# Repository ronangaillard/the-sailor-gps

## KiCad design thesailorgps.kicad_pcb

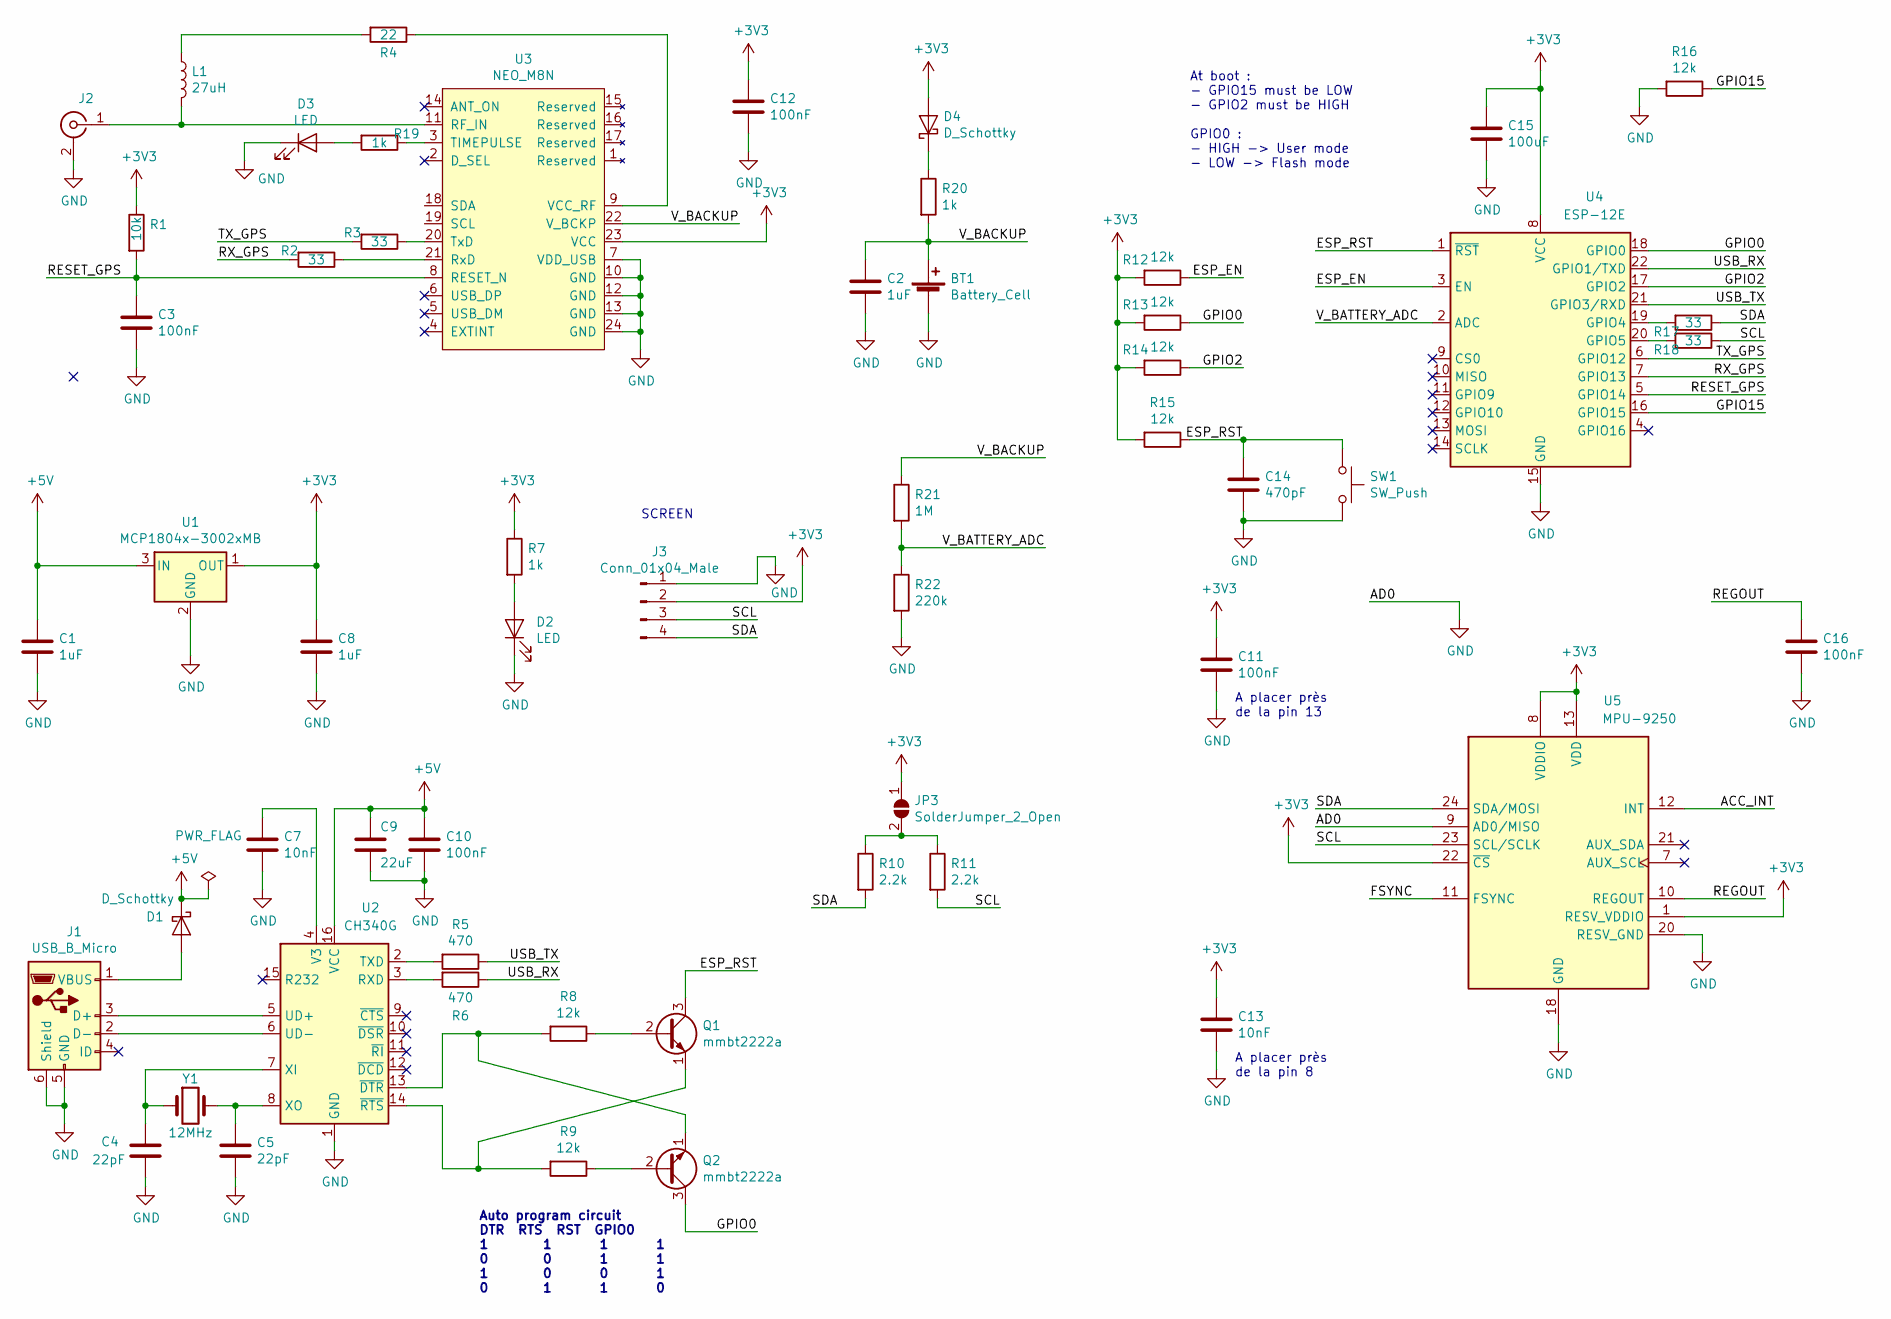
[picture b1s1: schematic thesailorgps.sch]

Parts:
BT1: Battery_Cell; 2998
C1, C2, C8: 1uF; C_0603_HandSoldering
C3, C10, C11, C12, C16: 100nF; C_0603_HandSoldering
C4, C5: 22pF; C_0603_HandSoldering
C7, C13: 10nF; C_0603_HandSoldering
C9: 22uF; C_0603_HandSoldering
C14: 470pF; C_0603_HandSoldering
C15: 100uF; C_0603_HandSoldering
D1, D4: D_Schottky; D_0603
D2, D3: LED; LED_0603_HandSoldering
J1: USB_B_Micro; MOLEX_105017-1001
J2: Conn_Coaxial; SMA_coude
J3: Conn_01x04_Male; Molex_PicoBlade_53261-0471_04x1.25mm_Angled
JP3: SolderJumper_2_Open; SolderJumper-2_P1.3mm_Open_RoundedPad1.0x1.5mm
L1: 27uH; L_0805_HandSoldering
Q1, Q2: mmbt2222a; SOT-23-3
R1: 10k; R_0603_HandSoldering
R2, R3, R17, R18: 33; R_0603_HandSoldering
R4: 22; R_0603_HandSoldering
R5, R6: 470; R_0603_HandSoldering
R7, R19, R20: 1k; R_0603_HandSoldering
R8, R9, R12, R13, R14, R15, R16: 12k; R_0603_HandSoldering
R10, R11: 2.2k; R_0603_HandSoldering
R21: 1M; R_0603_HandSoldering
R22: 220k; R_0603_HandSoldering
SW1: SW_Push; ebay_smd_button
U1: MCP1804x-3002xMB; SOT-89-3_Handsoldering
U2: CH340G; SOIC-16_3.9x9.9mm_Pitch1.27mm
U3: NEO_M8N; neo_m8n
U4: ESP-12E
U5: MPU-9250; QFN-24-1EP_3x3mm
Y1: 12MHz; Crystal_SMD_0603-2pin_6.0x3.5mm_HandSoldering

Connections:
+3V3: C8.1, C11.1, C12.1, C13.1, C15.1, D4.2 (A), J3.2, JP3.1 (A), R1.1, R7.1, R12.2, R13.2, R14.2, R15.2, U1.1 (OUT), U3.23 (VCC), U4.8 (VCC), U5.1 (RESV_VDDIO), U5.8 (VDDIO), U5.13 (VDD), U5.22 (~CS)
+5V: C1.1, C9.1, C10.1, D1.1 (K), U1.3 (IN), U2.16 (VCC)
/ACC_INT: U5.12 (INT)
/ESP_EN: R12.1, U4.3 (EN)
/ESP_RST: C14.1, Q1.3 (C), R15.1, SW1.1, U4.1 (~RST)
/FSYNC: U5.11 (FSYNC)
/GPIO0: Q2.3 (C), R13.1, U4.18 (GPIO0)
/GPIO2: R14.1, U4.17 (GPIO2)
/GPIO15: R16.1, U4.16 (GPIO15)
/REGOUT: C16.1, U5.10 (REGOUT)
/RESET_GPS: C3.1, R1.2, U3.8 (RESET_N), U4.5 (GPIO14)
/RX_GPS: R2.2, U4.7 (GPIO13)
/SCL: J3.3, R11.2, R18.1, U5.23 (SCL/SCLK)
/SDA: J3.4, R10.2, R17.1, U5.24 (SDA/MOSI)
/TX_GPS: R3.2, U4.6 (GPIO12)
/USB_RX: R6.1, U4.22 (GPIO1/TXD)
/USB_TX: R5.1, U4.21 (GPIO3/RXD)
/V_BACKUP: BT1.1 (+), C2.1, R20.2, R21.1, U3.22 (V_BCKP)
/V_BATTERY_ADC: R21.2, R22.1, U4.2 (ADC)
GND: BT1.2 (-), C1.2, C2.2, C3.2, C4.2, C5.2, C7.2, C8.2, C9.2, C10.2, C11.2, C12.2, C13.2, C14.2, C15.2, C16.2, D2.1 (K), D3.1 (K), J1.5 (GND), J1.6 (Shield), J2.2 (Ext), J3.1, R16.2, R22.2, SW1.2, U1.2 (GND), U2.1 (GND), U3.7 (VDD_USB), U3.10 (GND), U3.12 (GND), U3.13 (GND), U3.24 (GND), U4.15 (GND), U5.9 (AD0/MISO), U5.18 (GND), U5.20 (RESV_GND)
unnamed: C4.1, U2.7 (XI), Y1.1
unnamed: C5.1, U2.8 (XO), Y1.2
unnamed: C7.1, U2.4 (V3)
unnamed: D1.2 (A), J1.1 (VBUS)
unnamed: D2.2 (A), R7.2
unnamed: D3.2 (A), R19.2
unnamed: D4.1 (K), R20.1
unnamed: J1.2 (D-), U2.6 (UD-)
unnamed: J1.3 (D+), U2.5 (UD+)
unnamed: J2.1 (In), L1.2, U3.11 (RF_IN)
unnamed: JP3.2 (B), R10.1, R11.1
unnamed: L1.1, R4.2
unnamed: Q1.1 (E), R9.2, U2.14 (~RTS)
unnamed: Q1.2 (B), R8.1
unnamed: Q2.1 (E), R8.2, U2.13 (~DTR)
unnamed: Q2.2 (B), R9.1
unnamed: R2.1, U3.21 (RxD)
unnamed: R3.1, U3.20 (TxD)
unnamed: R4.1, U3.9 (VCC_RF)
unnamed: R5.2, U2.2 (TXD)
unnamed: R6.2, U2.3 (RXD)
unnamed: R17.2, U4.19 (GPIO4)
unnamed: R18.2, U4.20 (GPIO5)
unnamed: R19.1, U3.3 (TIMEPULSE)

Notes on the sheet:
SCREEN
Auto program circuit DTR RTS RST GPIO0 1 1 1 1 0 0 1 1 1 0 0 1 0 1 1 0
At boot : - GPIO15 must be LOW - GPIO2 must be HIGH GPIO0 : - HIGH -> User mode - LOW -> Flash mode
A placer près de la pin 13
A placer près de la pin 8

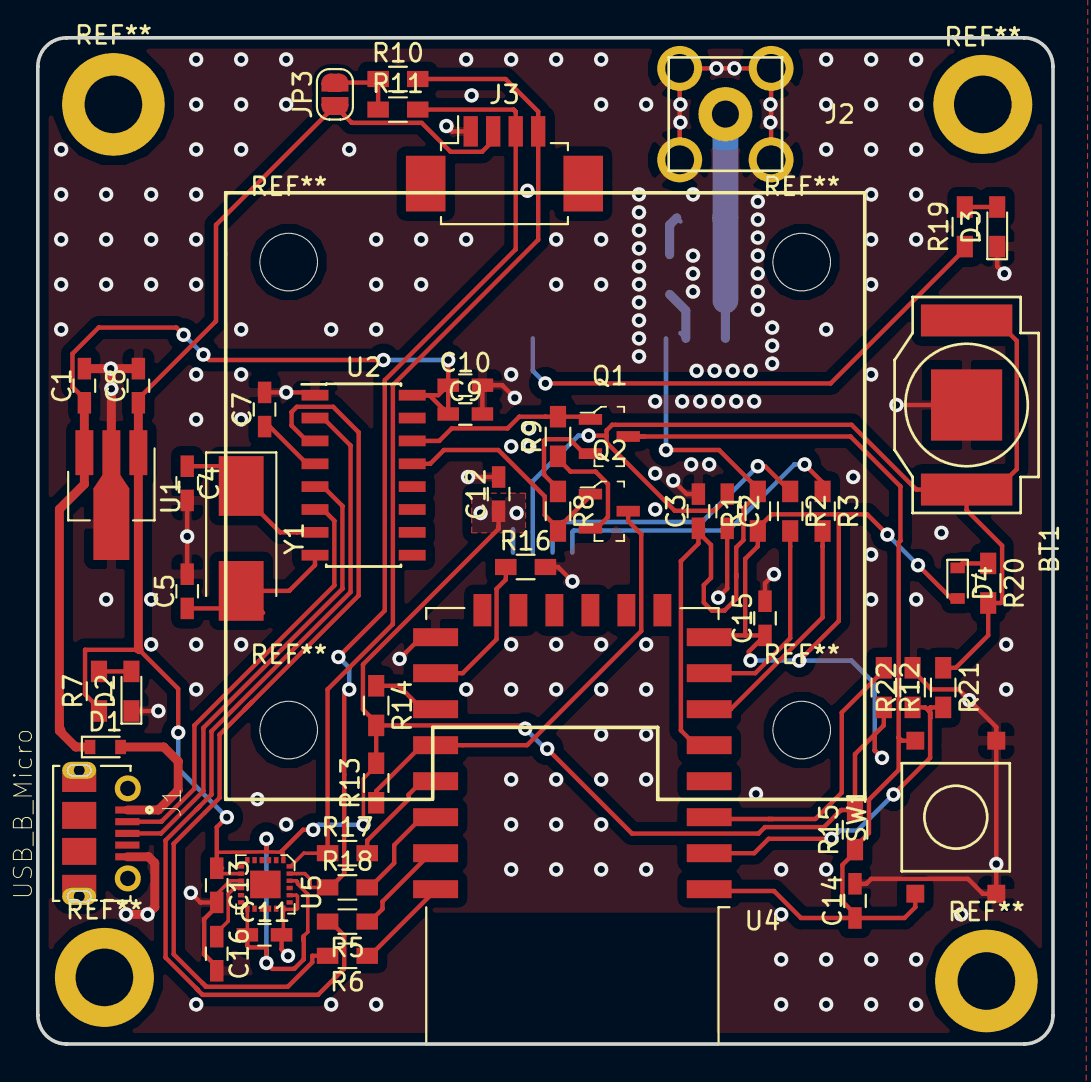
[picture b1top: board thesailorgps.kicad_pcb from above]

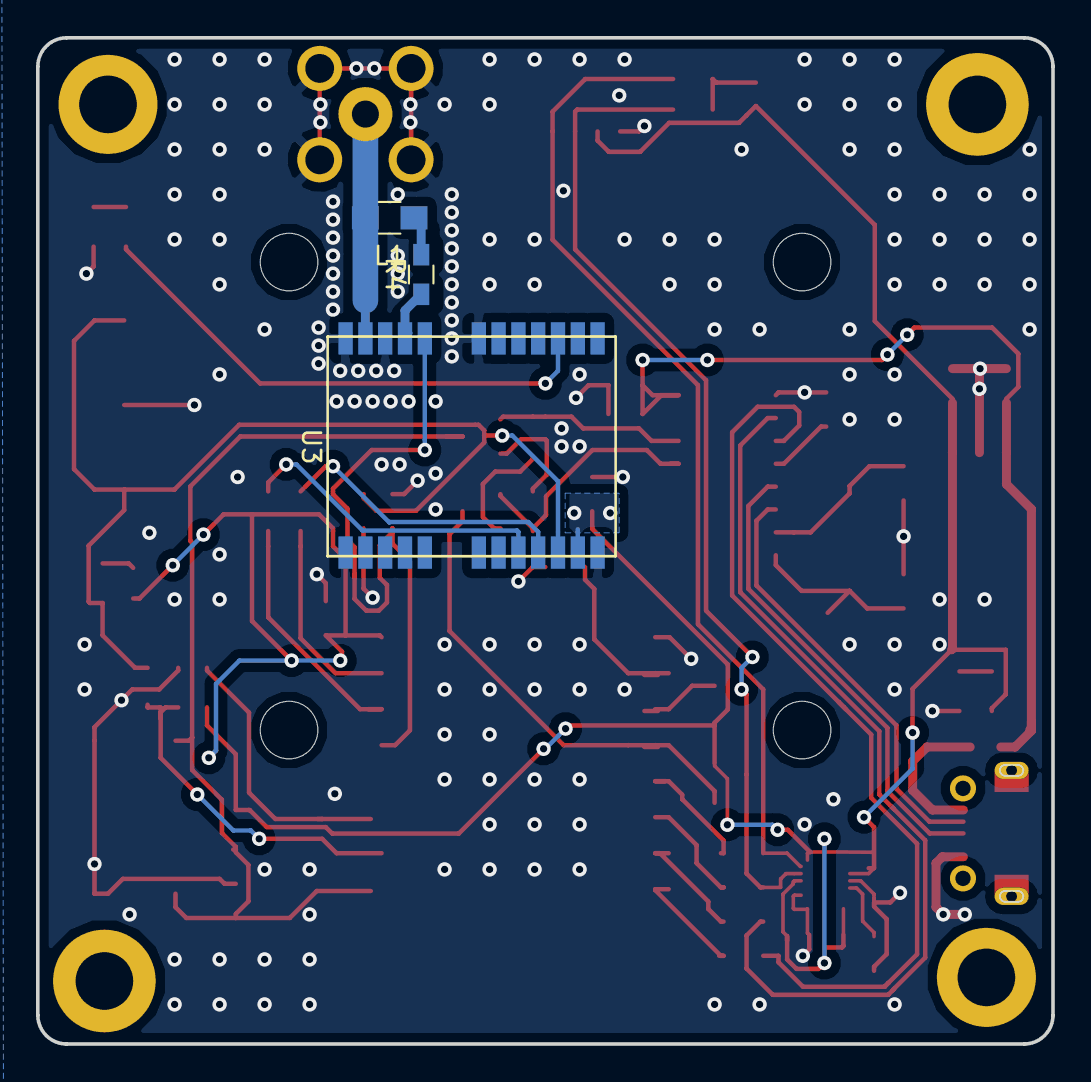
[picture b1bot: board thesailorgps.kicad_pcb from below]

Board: 2 copper layers, 56.4 x 55.9 mm, 56 parts (3 on the bottom side), 42 nets.

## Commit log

2018-11-15 Finished schem and started routing
2018-11-15 Improve routing
2018-11-18 Finished first routing
